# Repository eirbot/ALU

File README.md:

# ALU

Alu for the yet not named Eirbot computer

Lots of thing, not well organized

- Eagle schematics / Layouts for different version af the ALU
- VB.net (^^) for checking the design

Here is the document that resume the project : https://docs.google.com/document/d/e/2PACX-1vTW729kGLY1_6qNwQKunDP3PQwhFTjCwDQC52wJcxSMwBfEWZoxFu8FbD9BSjGNmGrzLaNSMzgS-qGt/pub

# TODO

- Définir l'architecture, le jeu d'instruction et les contraintes
- Il reste les registres, la stack, le décodeur d'instruction, la gestion des
  entrées-sorties, la RAM
- Clavier, souris, port série, VGA et stockage (floppy ou disque dur)

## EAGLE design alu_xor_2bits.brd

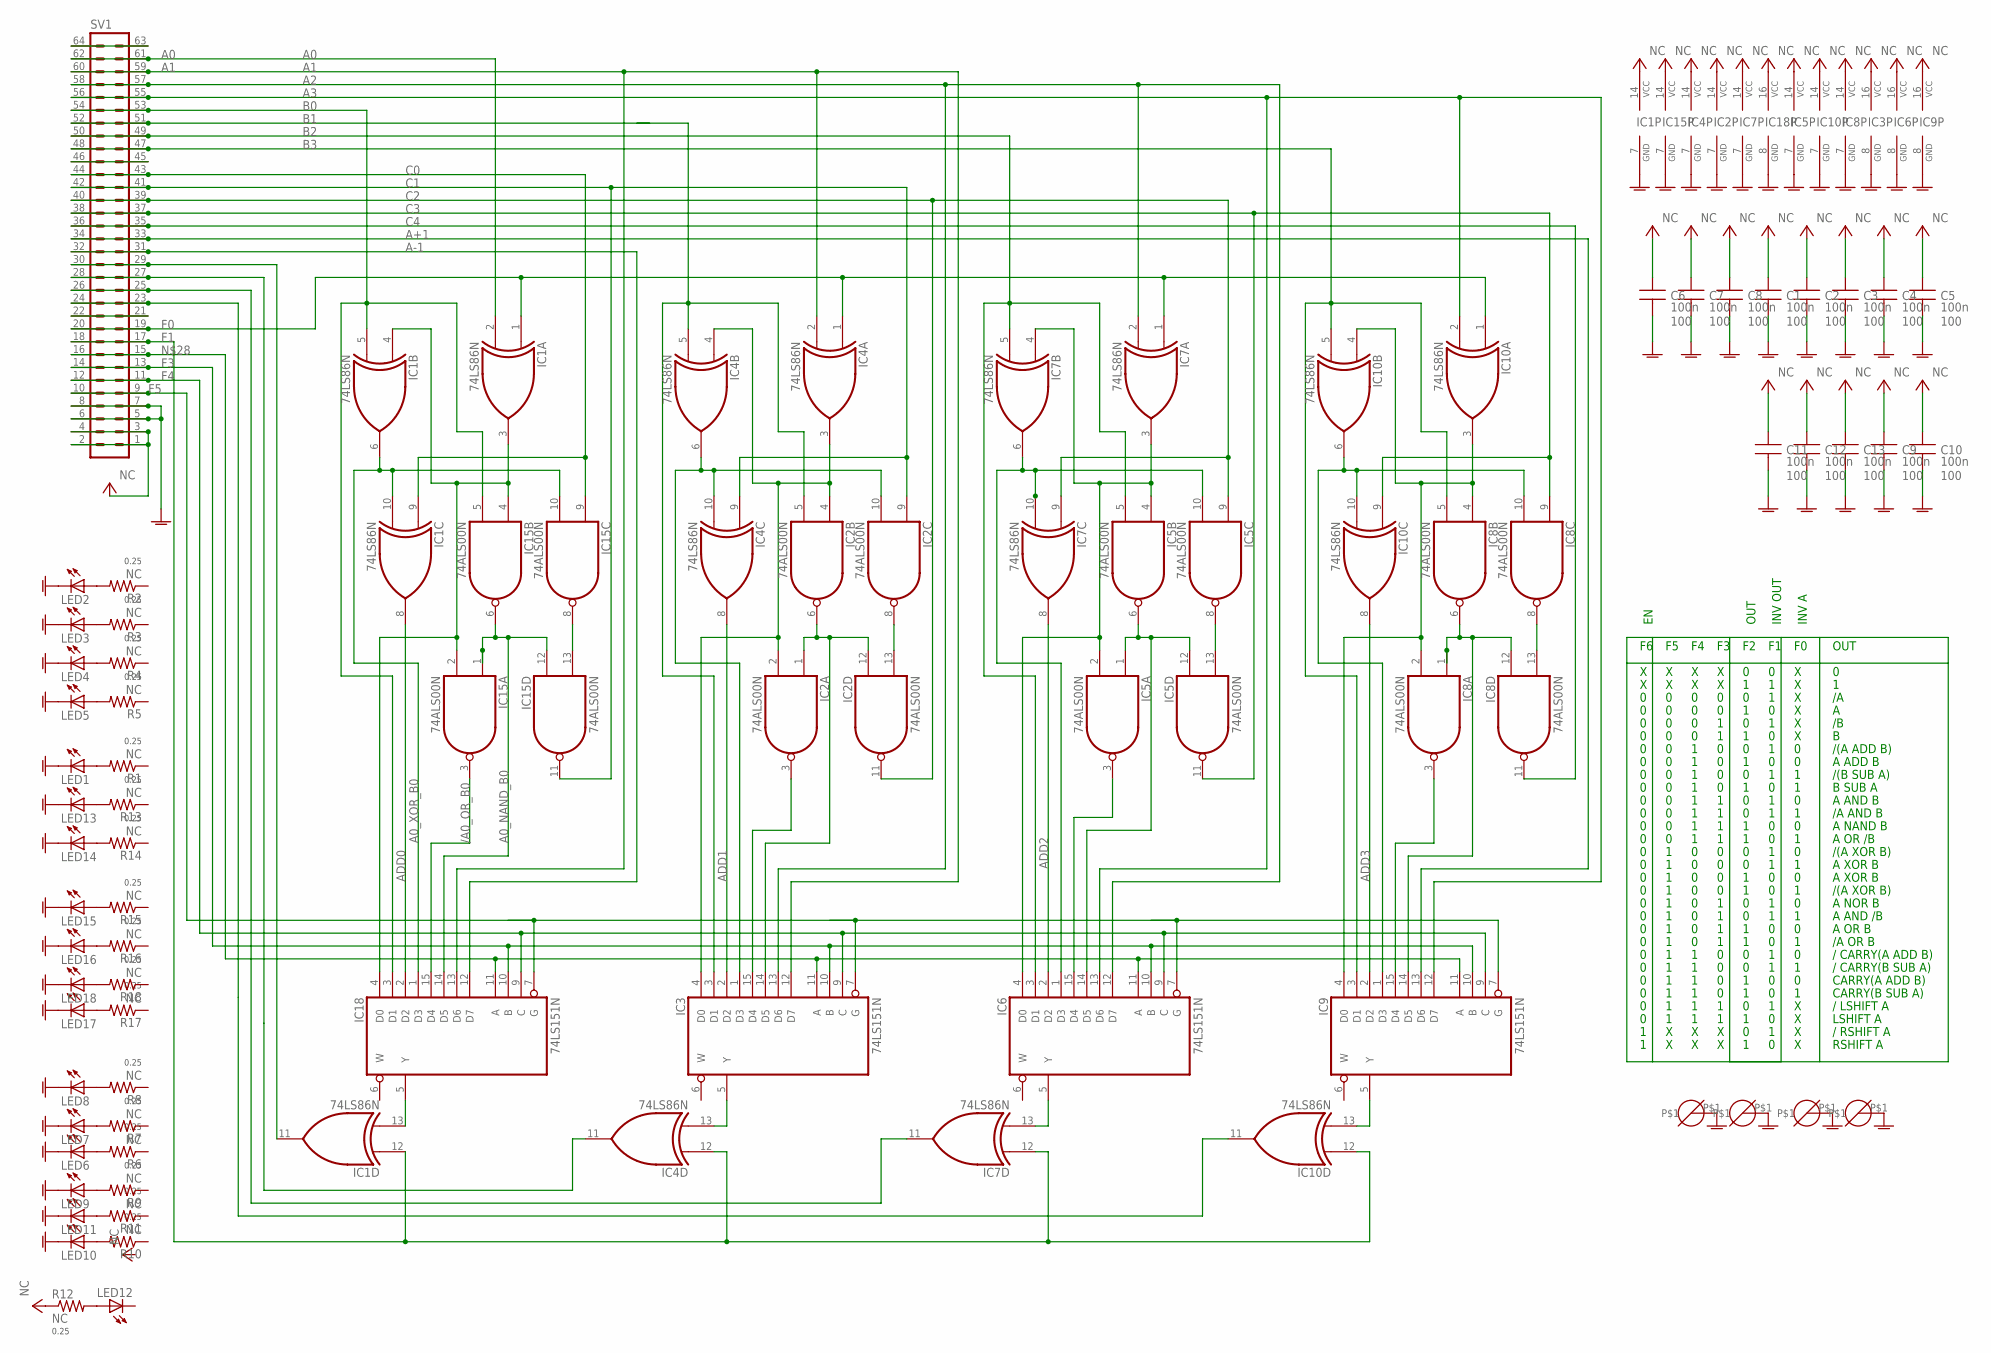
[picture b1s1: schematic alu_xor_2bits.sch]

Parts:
C1, C2, C3, C4, C5, C6, C7, C8, C9, C10, C11, C12, C13: 100n; C050-030X075
IC1, IC4, IC7, IC10: 74LS86N; DIL14
IC2, IC5, IC8, IC15: 74ALS00N; DIL14
IC3, IC6, IC9, IC18: 74LS151N; DIL16
LED1, LED2, LED3, LED4, LED5, LED6, LED7, LED8, LED9, LED10, LED11, LED12, LED13, LED14, LED15, LED16, LED17, LED18: LED3MM
R1, R2, R3, R4, R5, R6, R7, R8, R9, R10, R11, R12, R13, R14, R15, R16, R17, R18: NC; 0207/10
SV1: ML64L
U$1, U$2, U$3, U$4: BANANE_2; PAD_BANANE

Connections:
+5V: C1.1, C2.1, C3.1, C4.1, C5.1, C6.1, C7.1, C8.1, C9.1, C10.1, C11.1, C12.1, C13.1, IC1.14 (VCC), IC2.14 (VCC), IC3.16 (VCC), IC4.14 (VCC), IC5.14 (VCC), IC6.16 (VCC), IC7.14 (VCC), IC8.14 (VCC), IC9.16 (VCC), IC10.14 (VCC), IC15.14 (VCC), IC18.16 (VCC), R12.1, SV1.1, SV1.2, SV1.3, SV1.4
/A0_OR_B0: IC15.3 (O), IC18.15 (D4)
A0: IC1.2 (I1), SV1.61, SV1.62
A0_NAND_B0: IC15.1 (I0), IC15.6 (O), IC15.12 (I0), IC18.14 (D5)
A0_XOR_B0: IC1.6 (O), IC1.10 (I1), IC15.10 (I1), IC18.1 (D3)
A1: IC3.12 (D7), IC4.2 (I1), IC18.13 (D6), SV1.59, SV1.60
A2: IC3.13 (D6), IC6.12 (D7), IC7.2 (I1), SV1.57, SV1.58
A3: IC6.13 (D6), IC9.12 (D7), IC10.2 (I1), SV1.55, SV1.56
A+1: IC9.13 (D6), SV1.33, SV1.34
A-1: IC18.12 (D7), SV1.31, SV1.32
ADD0: IC1.8 (O), IC18.2 (D2)
ADD1: IC3.2 (D2), IC4.8 (O)
ADD2: IC6.2 (D2), IC7.8 (O)
ADD3: IC9.2 (D2), IC10.8 (O)
B0: IC1.5 (I1), IC15.5 (I1), IC18.3 (D1), SV1.53, SV1.54
B1: IC2.5 (I1), IC3.3 (D1), IC4.5 (I1), SV1.51, SV1.52
B2: IC5.5 (I1), IC6.3 (D1), IC7.5 (I1), SV1.49, SV1.50
B3: IC8.5 (I1), IC9.3 (D1), IC10.5 (I1), SV1.47, SV1.48
C0: IC1.9 (I0), IC15.9 (I0), SV1.43, SV1.44
C1: IC2.9 (I0), IC4.9 (I0), IC15.11 (O), SV1.41, SV1.42
C2: IC2.11 (O), IC5.9 (I0), IC7.9 (I0), SV1.39, SV1.40
C3: IC5.11 (O), IC8.9 (I0), IC10.9 (I0), SV1.37, SV1.38
C4: IC8.11 (O), SV1.35, SV1.36
F0: IC1.1 (I0), IC4.1 (I0), IC7.1 (I0), IC10.1 (I0), SV1.19, SV1.20
F1: IC1.12 (I0), IC4.12 (I0), IC7.12 (I0), IC10.12 (I0), SV1.17, SV1.18
F3: IC3.10 (B), IC6.10 (B), IC9.10 (B), IC18.10 (B), SV1.13, SV1.14
F4: IC3.9 (C), IC6.9 (C), IC9.9 (C), IC18.9 (C), SV1.11, SV1.12
F5: IC3.7 (G), IC6.7 (G), IC9.7 (G), IC18.7 (G), SV1.9, SV1.10
GNDA: C1.2, C2.2, C3.2, C4.2, C5.2, C6.2, C7.2, C8.2, C9.2, C10.2, C11.2, C12.2, C13.2, IC1.7 (GND), IC2.7 (GND), IC3.8 (GND), IC4.7 (GND), IC5.7 (GND), IC6.8 (GND), IC7.7 (GND), IC8.7 (GND), IC9.8 (GND), IC10.7 (GND), IC15.7 (GND), IC18.8 (GND), LED1.K (C), LED2.K (C), LED3.K (C), LED4.K (C), LED5.K (C), LED6.K (C), LED7.K (C), LED8.K (C), LED9.K (C), LED10.K (C), LED11.K (C), LED13.K (C), LED14.K (C), LED15.K (C), LED16.K (C), LED17.K (C), LED18.K (C), SV1.5, SV1.6, SV1.7, SV1.8, U$1.P$1, U$2.P$1, U$3.P$1, U$4.P$1
unnamed: SV1.45, SV1.46
unnamed: IC2.8 (O), IC2.13 (I1)
unnamed: LED1.A, R1.2
unnamed: IC1.3 (O), IC1.4 (I0), IC15.2 (I1), IC15.4 (I0), IC18.4 (D0)
unnamed: LED2.A, R2.2
unnamed: LED3.A, R3.2
unnamed: LED4.A, R4.2
unnamed: LED5.A, R5.2
unnamed: LED6.A, R6.2
unnamed: LED7.A, R7.2
unnamed: LED8.A, R8.2
unnamed: LED9.A, R9.2
unnamed: LED10.A, R10.2
unnamed: LED11.A, R11.2
unnamed: LED12.A, R12.2
unnamed: LED13.A, R13.2
unnamed: LED14.A, R14.2
unnamed: LED15.A, R15.2
unnamed: IC2.2 (I1), IC2.4 (I0), IC3.4 (D0), IC4.3 (O), IC4.4 (I0)
unnamed: LED16.A, R16.2
unnamed: IC1.13 (I1), IC18.5 (Y)
unnamed: LED17.A, R17.2
unnamed: LED18.A, R18.2
unnamed: IC3.5 (Y), IC4.13 (I1)
unnamed: IC3.11 (A), IC6.11 (A), IC9.11 (A), IC18.11 (A), SV1.15, SV1.16
unnamed: IC5.8 (O), IC5.13 (I1)
unnamed: IC1.11 (O), SV1.29, SV1.30
unnamed: SV1.63, SV1.64
unnamed: IC5.2 (I1), IC5.4 (I0), IC6.4 (D0), IC7.3 (O), IC7.4 (I0)
unnamed: IC6.5 (Y), IC7.13 (I1)
unnamed: IC2.10 (I1), IC3.1 (D3), IC4.6 (O), IC4.10 (I1)
unnamed: IC8.8 (O), IC8.13 (I1)
unnamed: IC8.2 (I1), IC8.4 (I0), IC9.4 (D0), IC10.3 (O), IC10.4 (I0)
unnamed: IC9.5 (Y), IC10.13 (I1)
unnamed: IC2.3 (O), IC3.15 (D4)
unnamed: IC2.1 (I0), IC2.6 (O), IC2.12 (I0), IC3.14 (D5)
unnamed: IC5.10 (I1), IC6.1 (D3), IC7.6 (O), IC7.10 (I1)
unnamed: IC5.1 (I0), IC5.6 (O), IC5.12 (I0), IC6.14 (D5)
unnamed: SV1.21, SV1.22
unnamed: IC10.11 (O), SV1.23, SV1.24
unnamed: IC7.11 (O), SV1.25, SV1.26
unnamed: IC4.11 (O), SV1.27, SV1.28
unnamed: IC5.3 (O), IC6.15 (D4)
unnamed: IC8.3 (O), IC9.15 (D4)
unnamed: IC8.1 (I0), IC8.6 (O), IC8.12 (I0), IC9.14 (D5)
unnamed: IC8.10 (I1), IC9.1 (D3), IC10.6 (O), IC10.10 (I1)
unnamed: IC15.8 (O), IC15.13 (I1)

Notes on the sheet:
INV A
INV OUT
OUT
/(A ADD B)
A ADD B
/(B SUB A)
B SUB A
/A AND B
A AND B
A NAND B
A OR /B
/(A XOR B)
A XOR B
A NOR B
A AND /B
A OR B
/A OR B
/ CARRY(A ADD B)
/ CARRY(B SUB A)
CARRY(A ADD B)
CARRY(B SUB A)
/ LSHIFT A
LSHIFT A
/ RSHIFT A
RSHIFT A

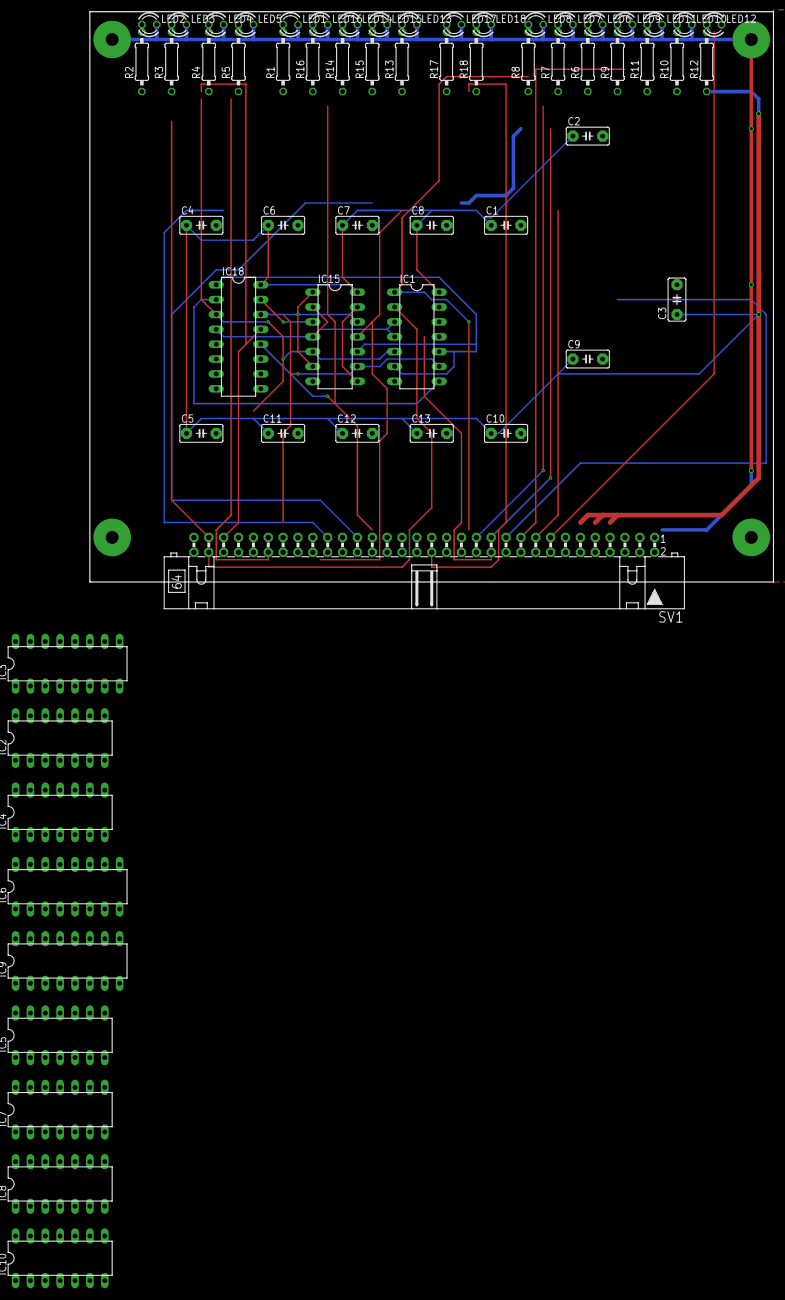
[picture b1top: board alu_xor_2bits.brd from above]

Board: 2 copper layers, 116.8 x 97.5 mm, 66 parts (0 on the bottom side), 76 nets.

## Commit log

2019-08-24 computing prop delay... Brute force way
2019-08-24 computing prop delay more efficently
2019-08-24 add functionality check
2019-09-12 Add todo list

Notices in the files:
parts and their libraries:
MDE: All rights reserved
